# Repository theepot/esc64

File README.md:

esc64
=====

Simulation, assembler, emulator and other software as part of the ESC64 project.

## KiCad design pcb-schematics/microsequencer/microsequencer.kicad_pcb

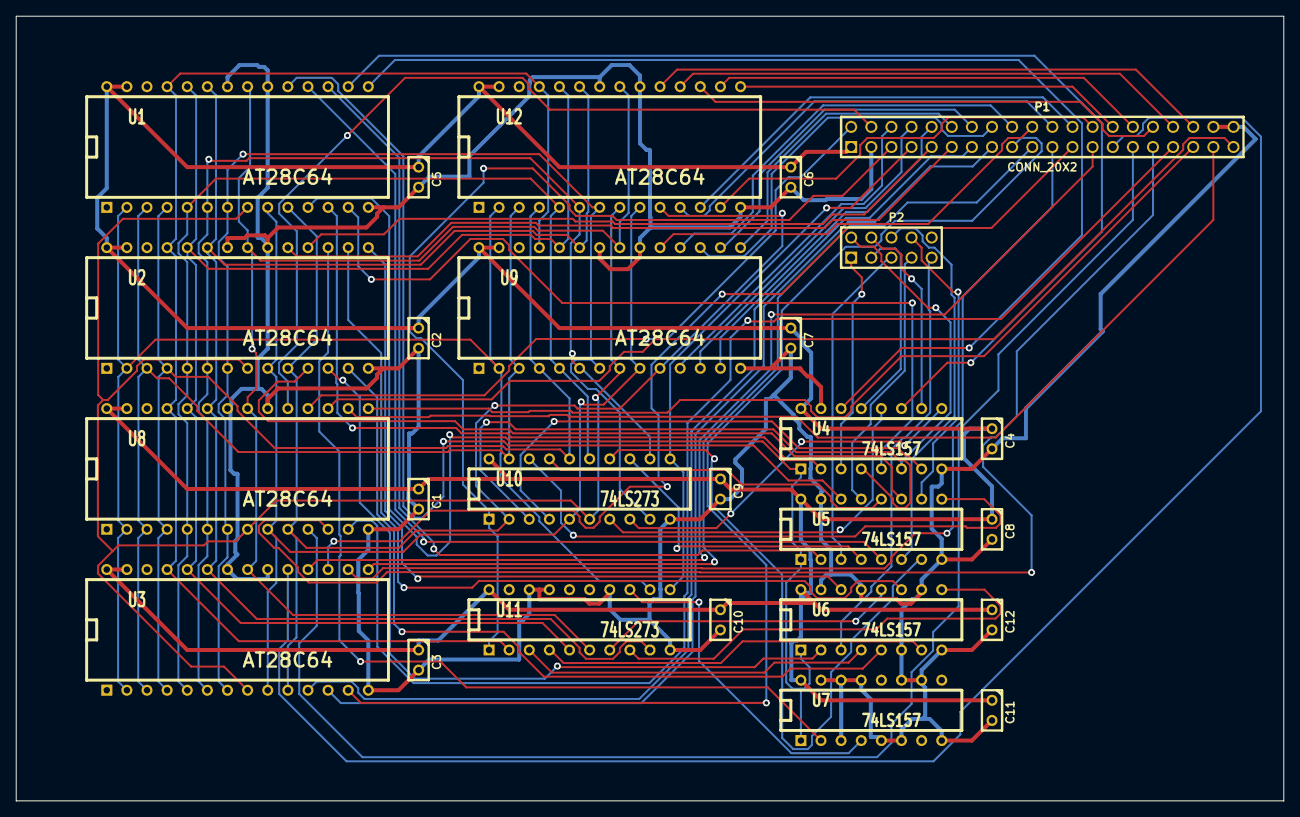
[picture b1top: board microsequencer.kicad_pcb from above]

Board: 2 copper layers, 160.0 x 99.1 mm, 26 parts (0 on the bottom side), 87 nets.

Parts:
C1, C2, C3, C4, C5, C6, C7, C8, C9, C10, C11, C12: CP1; C1
P1: CONN_20X2; PIN_ARRAY_20X2
P2: CONN_10; PIN_ARRAY_5x2
U1, U2, U3, U8, U9, U12: AT28C64; DIP-28__600
U4, U5, U6, U7: 74LS157; DIP-16__300
U10, U11: 74LS273; DIP-20__300

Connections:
/A0: U1.10, U2.10, U3.10, U8.10, U9.10, U10.2, U12.10
/A1: U1.9, U2.9, U3.9, U8.9, U9.9, U10.5, U12.9
/A2: U1.8, U2.8, U3.8, U8.8, U9.8, U10.6, U12.8
/A3: U1.7, U2.7, U3.7, U8.7, U9.7, U10.9, U12.7
/A4: U1.6, U2.6, U3.6, U8.6, U9.6, U10.12, U12.6
/A5: U1.5, U2.5, U3.5, U8.5, U9.5, U10.15, U12.5
/A6: U1.4, U2.4, U3.4, U8.4, U9.4, U10.16, U12.4
/A7: U1.3, U2.3, U3.3, U8.3, U9.3, U10.19, U12.3
/A8: U1.25, U2.25, U3.25, U8.25, U9.25, U11.2, U12.25
/A9: U1.24, U2.24, U3.24, U8.24, U9.24, U11.5, U12.24
/A10: U1.21, U2.21, U3.21, U8.21, U9.21, U11.6, U12.21
/A11: U1.23, U2.23, U3.23, U8.23, U9.23, U11.9, U12.23
/A12: U1.2, U2.2, U3.2, U8.2, U9.2, U11.12, U12.2
/C0: P1.9, U2.18
/C1: P1.11, U2.19
/C2: P1.13, U3.11
/C3: P1.15, U3.12
/C4: P1.17, U3.13
/C5: P1.19, U3.15
/C6: P1.21, U3.16
/C7: P1.23, U3.17
/C8: P1.25, U3.18
/C9: P1.27, U3.19
/C10: P1.29, U8.11
/C11: P1.31, U8.12
/C12: P1.33, U8.13
/C13: P1.35, U8.15
/C14: P1.37, U8.16
/C15: P1.39, U8.17
/C16: P1.2, U8.18
/C17: P1.4, U8.19
/C18: P1.6, U9.11
/C19: P1.8, U9.12
/C20: P1.10, U9.13
/C21: P1.12, U9.15
/C22: P1.14, U9.16
/C23: P1.16, U9.17
/C24: P1.18, U9.18
/C25: P1.20, U9.19
/C26: P1.22, U12.11
/C27: P1.24, U12.12
/C28: P1.26, U12.13
/C29: P1.28, U12.15
/C30: P1.30, U12.16
/C31: P1.32, U12.17
/C32: P1.34, U12.18
/C33: P1.36, U12.19
/carry: P2.2, U4.6
/op0: P2.3, U4.13
/op1: P2.4, U4.10
/op2: P2.5, U5.3
/op3: P2.6, U5.6
/op4: P2.7, U5.13
/op5: P2.8, U5.10
/op6: P2.9, U6.3
/zero: P2.1, U4.3
GND: C1.2, C2.2, C3.2, C4.2, C5.2, C6.2, C7.2, C8.2, C9.2, C10.2, C11.2, C12.2, P1.3, P1.38, P1.40, U1.14, U1.20, U1.22, U2.14, U2.20, U2.22, U3.14, U3.20, U3.22, U4.8, U4.15, U5.8, U5.15, U6.6, U6.8, U6.10, U6.13, U6.15, U7.3, U7.5, U7.6, U7.8, U7.10, U7.11, U7.13, U7.14, U7.15, U8.14, U8.20, U8.22, U9.14, U9.20, U9.22, U10.10, U11.10, U11.14, U11.17, U11.18, U12.14, U12.20, U12.22
unnamed: P1.5, U10.1, U11.1
unnamed: P1.7, U10.11, U11.11
unnamed: U5.4, U10.13
unnamed: U5.9, U10.18
unnamed: U5.12, U10.17
unnamed: U5.7, U10.14
unnamed: U4.9, U10.8
unnamed: U4.12, U10.7
unnamed: U4.7, U10.4
unnamed: U4.4, U10.3
unnamed: U7.4, U11.13
unnamed: U6.9, U11.8
unnamed: U6.12, U11.7
unnamed: U6.7, U11.4
unnamed: U6.4, U11.3
unnamed: U1.19, U5.14
unnamed: U2.13, U6.5
unnamed: U2.11, U5.11
unnamed: U2.12, U6.2
unnamed: U2.16, U6.11
unnamed: U2.15, U6.14
unnamed: U1.11, U4.1, U5.1, U6.1, U7.1
unnamed: U1.12, U4.2
unnamed: U1.13, U4.5
unnamed: U1.16, U4.11
unnamed: U2.17, U7.2
unnamed: U1.15, U4.14
unnamed: U1.17, U5.2
unnamed: U1.18, U5.5
VCC: C1.1, C2.1, C3.1, C4.1, C5.1, C6.1, C7.1, C8.1, C9.1, C10.1, C11.1, C12.1, P1.1, U1.27, U1.28, U2.27, U2.28, U3.27, U3.28, U4.16, U5.16, U6.16, U7.16, U8.27, U8.28, U9.27, U9.28, U10.20, U11.20, U12.27, U12.28

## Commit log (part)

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2012-10-08 testing commit
2012-10-08 removed test file as part of a test :)
2012-10-08 added the assembler
2012-10-09 added inital verilog models
2012-10-09 added behavioural simulation for the program counter
2012-10-11 added CPU stub (not working yet) and renamed some files
2012-10-11 added microsequencer verilog files
2012-10-12 finishes cpu declarations. doesn't have a testbench yet.
2012-10-12 forgot a few files
2012-10-14 improved assembler scanner a bit.
2012-10-16 updated CPU simulation
2012-10-16 merged with own version of mSeq.v
2012-10-17 scanner is finished (enough) to be used by parser
2012-10-18 cpu seems to work now. need to clean up though
2012-10-18 Deleted left over files from previous commit
2012-10-19 Improved cpu.v and wrote microcode for fetch, add, mov, movlit. Added status verilog module.
2012-10-22 improved alu testbench.
2012-10-23 made regsel testbench
2012-10-23 added opcodes.h. improved urom generator
2012-10-23 implemented remaining instructions in microcode
2012-10-23 added cpu.h, which now contains most definitions that were first in gen_urom_.c
2012-10-23 updated .gitignore to ignore generateble files
2012-10-23 Fixed some mistakes in previous commit.
2012-10-25 fixed syntax error :O
2012-10-25 added structural model of PGregister. The cpu now uses it. Put delay in mSeq and PC so the cpu still works. LR is now register 6. SP deleted. GP5 added.
2012-10-25 revised hashmap to hashset. created symtable stub. misc other things
2012-10-26 corrected ir and status makefiles
2012-10-26 added simulations for 4to1 and 2to1 multiplexors
2012-10-28 added *.lst to ignore
2012-10-29 updated some ignore rules
2012-10-29 added 3 to 8 decoder sim
2012-10-29 Fixed mistake in Quad2To1Mux_74157.
2012-10-30 added structural sim for pc
2012-10-30 Added QuadCounter_74163 verilog model
2012-10-30 Added structural ALU model. Updated CPU.
2012-10-31 added virtual machine to git repo
2012-11-01 cpu test program, to test ALU. Fixed cpu.v and alu_common.h
2012-11-01 fixed mistake in urom. added shift operations. updated test program.
2012-11-05 v 0.1 of VM with GUI
2012-11-06 did some bugfixes/cleaning up, implemented part of object file access (still needs testing)
2012-11-08 worked on objectstream stuff, not finished
2012-11-10 Completed structural model of microsequencer. Added TODO file. Cleaned up itialise_field_descriptions() in uassembler.h
2012-11-10 object code writing/reading should work now, haven't tested everything yet. Also unit-tests should be improved
2012-11-13 improved objectcode unit-test a bit.
2012-11-15 added schematics for IR
2012-11-15 added status register schematics, fixed IR symbol
2012-11-16 changed design of ALU. Added schematics of ALU and GPRegister
2012-11-20 added schematics for register file and sram
2012-11-20 fixed pinseq errors with script. script is also attached :)
2012-11-20 brok sram by accident, fixed now
2012-11-20 fixed some errors in the gschem symbol files
2012-11-21 changed timings of 74xxx chips. Added transistion time
2012-11-21 completed objfile unit-test. added shoddy makefile
2012-11-21 added hashtable with reserved words (still need to incorporate in scanner). made unit test for reserved word table
2012-11-22 Updated unit-test a bit. scanner now uses new reserved words table
2012-11-23 Worked on parser for a bit. No working version yet
2012-11-27 added cpu schematic. Added refdes's attributes to most devices. Renamed some microsequencer controll lines.
2012-12-10 fixed stupid mistake in PC
2012-12-11 fixed yet another stupid mistake in register selection
2012-12-12 Completed circuit tester. Fixed small mistakes in some schematics
2012-12-12 added more tests for ALU
2012-12-18 added code to program EEPROMs
2012-12-21 fixed
2012-12-22 Create LICENSE
2013-01-02 changed numerous things on assembler.
2013-01-04 added incomplete bootstrap, computer and atmega328p schematics
2013-01-08 added EEPROM programmer and circuit tester. made changes to microassembler. Microassembler is incomplete
2013-01-10 added registers stack circuit test. Changed small thing in program counter circuit test.
2013-01-11 added initial version of bootstrapper software.
2013-01-15 updated ALU and ALU test
2013-01-17 completed new uassembler. changed design ALU. Changed computer schematic
2013-01-21 Added code to write/read executables. Remains to be tested
2013-01-22 added temporary notes
2013-01-23 deleted binary and updated .gitignore files
2013-01-23 added needed libserial. Modified bootstrapper and EEPROM programmer's makefile to link statically with libserial
2013-01-23 fixed libserial's Makefile
2013-01-24 modified mini assembler to be more convenient
2013-01-24 added new test programs. updated .gitignore to exclude .a files. fixed urom
2013-01-26 Added test programs for 'cmp', 'shift', 'and', 'or', 'xor' and conditional 'mov''s. Reorganized building of program's with mini_assembler. Added upload and download functionality to the bootstrapper'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
2013-01-26 added test for writing & reading executables. The test succeeds
2013-01-29 Added faster prime calculation program. Added new TOOD's. Fixed small bug in bootstrapper
2013-01-29 updated parser to work - or at least compile - with the new objectcode
2013-01-31 added more instructions. Fixed ALU test. Added monitor wires in computer.v
2013-02-11 lots of new assembler stuff
2013-02-14 updated gitignore for assembler subdirs
2013-02-15 linker doesn't seem to work yet
2013-02-15 fixed some stuff in linker. doesn't work properly yet though.
2013-02-25 added instructions, added read/write signal register. added dev_usart pheripheral code and schematics. Not tested yet
2013-02-26 exedump added
2013-03-04 rewrote most linker code, fixed freelist
2013-03-05 version 1 of assembler + linker finished
2013-03-05 added exception for Makefile and committed Makefile
2013-03-17 did some bugfixing in assembler, wrote multiplication routine (untested)
2013-03-17 fixed stupid bug with conditional branches, made 16x16=16bit multiplication routine
2013-03-18 relocated assemblt programs, wrote read routine for RPN demo, updated esc-asm makefile
2013-03-22 made verilog sim interactive mode stub
2013-04-26 makefile
2013-04-28 Removed dbus server stub in favaor of thrift server :)
2013-05-14 made bunch of changes to the way instructions and directives are described/handled in the assembler
2013-05-17 fixed some stuff in the assembler. did some work on sim thrift server. made quicksort for esc
2013-05-18 fixed opcode translation to opcode names
2013-06-06 Big update to assembler. Also some changes to sim and thrift server. Created ruby thrift client for quick testing
2013-06-06 fixed some schematics.
2013-08-07 It is now possible to write expressions in esc-assembly Thrift server for simulation is now working + small ruby client
2013-08-07 Forgot some (most) files in my last commit.
2013-10-23 minor fixes to build and pstring
2013-11-12 changed directory structure of simulation.
2013-11-25 Updated assembler with generator for instruction descriptions. added some test assembly programs.
2013-11-28 fixed mistake in assembler expression parsing. assembler now uses generated instructions/directives kwgen can generate decompilation info for the assembler (and third parties), assembler doesn' use i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
2013-12-14 added example for use during college
2013-12-15 mul.s contains C program equivalent
2013-12-15 added a bit of explanation
2013-12-19 Some small changes
2013-12-21 Fixed assembler CMakeLists. genkeywords and gendecomp are now dependencies of esc-asm-common. cleaned up sim thrift server code a bit.
2014-01-05 hope this didn't go horribly wrong...
2014-01-05 forgot one
2014-01-10 new section allocation stuff works now, alignment directive works as well
2014-01-12 moved virtualio into seperate lib, so later it can be used by the vm.
2014-01-12 removed old generated file.
2014-01-13 kwgen can now emit a header with opcode #defines in it
2014-01-15 added new vm. moved and modified kwgen. now generates instruction info previously present in cpu.h. removed ruby sim interface.
2014-01-17 implemented thrift service for vm. changed ram image format to list of bytes. changed thrift interface for cpu. changed trift implementation for the simulation
2014-01-20 implemented getMemory in vm and sim
2014-01-22 fixed absolute path in mini assembler makefile
2014-01-23 created scripts that compare the vm with the simulation. fixed some errors in the vm and sim.
2014-01-24 added some more instruction descriptions
2014-01-24 added version 0.1 of esc63 c runtime
2014-01-24 added first sample c program: fib.c! wonder if it works...
2014-01-25 forgot a file
2014-01-25 more fibonacci
2014-01-27 made pseudo instructions pseudo in infogen. added very ugly buildscript to lib.
2014-01-27 implemented ldb and stb. added -p option to sim and vm. fixed some things
2014-01-29 fixed a concurrency bug in the vm
2014-01-30 added inspect_cpu interface. regular cpu tests passed
2014-01-30 removed all abstract simulation stuff
2014-01-31 added c-programs for esc: conv, con2reg, prime-test, switchtest added common c-program code assembler now uses generated dissassembly info
2014-01-31 added sign extension instruction. tested. added scmp for sim. UNTESTED. updated ALU schematics.
2014-02-01 added esccrt.h implemented all routines + error handling stuff in esccrt.s
2014-02-02 added a virtual input & output stream device.
2014-02-02 fixed cmemcpy, made mistake accessing arguments, also didn't return dest pointer
2014-02-02 Update esccrt.h
    fixed prototype of cmemcpy
    committed using web interface :D
2014-02-03 tested scmp. added vis&vos arguments to the vm. fixed test-virtualiostream.c
2014-02-04 added io procedures for esc64 + test program for output routiens
2014-02-05 added test to check that lcc didn't make static identifiers global
2014-02-07 fixed bug in microrom
2014-02-07 fixed bug in escio routine io_in. added stdesc: contains various libc functions. ported wumpus (a game) infogen can now generate html docs for assembler directives and instructions
2014-02-16 finally added usage printing stuff to assembler executables
2014-02-16 added fputs and putchar. fixed rand. the negative rooms bug in wumpus is fixed because rand now no longer returns negative integers
2014-02-16 forgot 2 files
2014-02-18 made nice generic makefile. rules now throw out corrupt results. made makefile-template
2014-02-18 added base64 encoder/decoder + test
2014-02-19 added advent (doesn't work yet) updated some makefiles
2014-02-21 added script that builds everything in the repo
2014-02-28 assembler now switches around r5 and r6, because the microcode still uses r5 as sp exetolst now pads empty space with xxxxxxxx instead of 00000000 added pcallones test program
2014-02-28 changed sim makefile so that it copies urom from uassembler
2014-03-02 fixed some formatting in build-all.py
2014-03-02 added c programs, added some succes/failure messages
2014-03-04 made horrible mistake in quickfix in scanner
2014-03-18 assembler now no longer switches around r5 and r6
2014-04-07 esccrt2.inc makes use of m4 instead of gpp prime-demo is the demo used in Lukas' thesis presentation
2014-04-16 added option to print unlinked symbols in objdump made m4 makefile for c-programs fixed printf (behaved like sprintf before) added mvo macro to esccrt2.inc
2014-04-16 updated most c programs' makefile to use m4, also updated crt to use m4.
2014-04-20 added tanky game (beware, it's very very very slow)
2014-04-20 made some small optimizations to tanky
2014-04-22 made assembly routine to set cursor position in terminal. it's a lot faster, but can only handle coordinates in the range [0,99]
2014-08-23 added c lib for multiple contexts of execution
